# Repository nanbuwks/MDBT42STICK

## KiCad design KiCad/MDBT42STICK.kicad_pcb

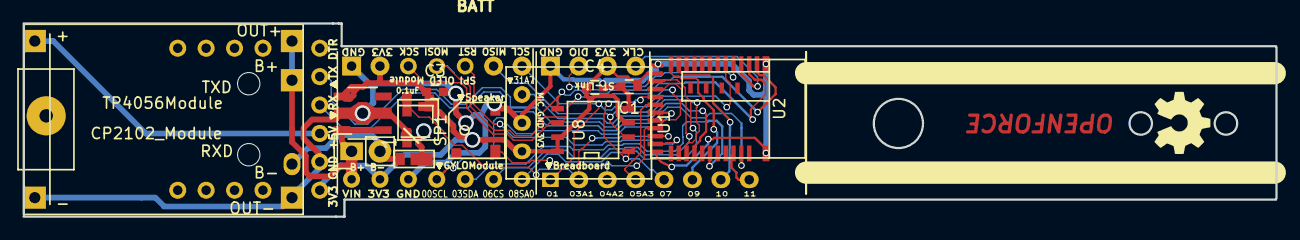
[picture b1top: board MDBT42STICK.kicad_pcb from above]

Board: 2 copper layers, 112.0 x 17.3 mm, 19 parts (0 on the bottom side), 28 nets.

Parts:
BT1: Battery; Pin_Header_Straight_1x02
C1, C3: 0.1uF; C_0603
C4: 2.2uF; C_0603
D1: D_Schottky; TUMD2
OSHW: 1.1; OSHW_LOGL_SYLK_5mm
P1: CONN_01X04; Pin_Header_Straight_1x04
P2: CONN_01X08; SolderWirePad_Circle_8xInline_0-85mmDrill
P3: OLED_0.96in_SPI; SolderWirePad_Circle_7xInline_0-85mmDrill
P4: CONN_01X01; Pin_Header_Straight_1x01
SP1: SPEAKER; PassiveBuzzerSMD_JiangsuHuaneng_MLT-5030
U1: ADMP401Module; ADMP401_Module
U2: MDBT42
U3: addressableLEDchip; addressableLEDchip3535
U4: CP2102_Module; CP2102Module
U5: GY-LSM6DS3Module
U6: TP4056Module
U7: NJM2884U; SOT89-5_Housing
U8: 25LC_EEPROM; SOIC-8-N

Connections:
+3V3: C1.1, C3.1, C4.1, P1.3, P3.2, U1.3, U2.15, U3.3, U4.1, U5.2, U7.4, U8.3, U8.7, U8.8
GND: C1.2, C3.2, C4.2, P1.1, P3.1, SP1.2, U1.2, U2.1, U2.14, U2.25, U2.37, U3.1, U4.2, U5.3, U6.2, U6.6, U7.2, U8.4
unnamed: BT1.1, U5.1, U6.3, U6.4, U7.1, U7.5
unnamed: BT1.2, D1.2, U6.5
unnamed: D1.1, P4.1
unnamed: P1.2, U2.5
unnamed: P1.4, U2.4
unnamed: P2.1, P3.7, U2.21
unnamed: P2.2, U2.23, U3.2
unnamed: P2.3, SP1.1, U2.22
unnamed: P2.4, U2.19
unnamed: P2.5, U2.18, U8.1
unnamed: P2.6, U2.13
unnamed: P2.7, U2.12
unnamed: P2.8, U2.34
unnamed: P3.3, U2.3, U8.6
unnamed: P3.4, U2.2, U8.5
unnamed: P3.5, U2.24
unnamed: P3.6, U2.6, U8.2
unnamed: U2.8, U2.30
unnamed: U1.1, U2.28
unnamed: U2.16, U5.7
unnamed: U2.17, U5.6
unnamed: U2.20, U5.4
unnamed: U2.29, U4.5
unnamed: U2.31, U5.5
unnamed: U2.35, U4.4
unnamed: U4.3, U6.1

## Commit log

2018-07-10 2nd version.
2018-07-27 20180525 Version. Size Reduce.
2018-08-16 20180727 Version. Documents add and modify full color LED.
